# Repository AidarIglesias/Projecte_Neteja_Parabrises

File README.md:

# Projecte Eines De Disseny  
## Sistema de Neteja-Parabrises D'Un Automobil  
###### David Miravent, Biel Hornas, Aidar Iglesias  

### Objectiu  
Aquest projecte te com a objectiu dissenyar el l'entorn electronic que conforma el sistema de neteja-parabrises d'un automobil.  

El projecte estara dividit en 7 parts:  

1. Diagrama de blocs i components
2. Esquematic i simulacions
3. Placement i routing (layout v1)
4. Pre-entega (layout v2)
5. Entrega final (layout v3)
6. Muntatge i soldadura
7. Test PCB  

----  

### Caracteristiques i epecificacions  
El sistema de neteja-parabrises te com a caracteristica principal, com ja diu el seu nom, netejar la lluna del parabrises. Com que aquest sistema sera part d'un conjunt de ECUs (Electronic Control Unit) d'un automobil, hi ha un serie d'elements que tots ells tindran en comu:  

* Una etapa de regulacio de tensio (es fara servir [L78S05CV])
* Un microcontrolador (es fara servir un [PIC18F2580] de 28 pins) encarregat del control del nostre modul i de la comunicacio amb els altres
* Un bus de programacio i debug del microcontrolador
* Un bus [CAN] que permet la comunicacio sincrona amb els altres moduls
* Un bus [I2C] (o be [SPI]) per a la comunicacio sincrona interna del nostre modul
* Un bus de comunicacio [USART] que permet monitoritzar el sistema des d'un ordinador extern
* Una botonera per permetre la interaccio entre l'usuari i el modul

El sistema ha de complir les seguents **especificacions**:  

* Dos motors amb el seu final de carrera
* Dues bombes de liquid neteja-parabrises
* Sensor digital de pluja
* Calefactor del vidre

----  

### Funcionament  

El sistema al complet estara controlat per el microcontrolador. Per al moviment dels neteja parabrises, es faran servir dos motors, un per davant i un per darrere. Aquests motors estaran controlats per uns drivers, els quals subministren el corrent necessari per activar uns reles que faran girar els motors en un sentit o en l'altre. Quan l'usuari desitgi o quan el sensor de pluja detecti pluja, el microcontrolador enviara el senyal d'activacio dels motors. Tambe s'incloura un sistema de final de carrera, que indicara quan s'ha acabat el trajecte de la escombreta del neteja-parabrises i la fara canviar de sentit.  

El sistema tambe implementa dues bombes de liquid neteja-parabrises, cadascuna d'elles controlada per un driver i un rele. Aquestes s'activaran quan el conductor ho desitgi i funcionaran de la mateixa manera que el neteja-parabrises: mitjançant un motor.  

Hi haura un mode de neteja automatic, accionat per un sensor digital de pluja. Quan es detecti pluja. Aleshores, el neteja-parabrises es posara en funcionament.  

Hi ha quatre opcions a escollir:
* Activar motor neteja-parabrises davanter
* Activar motor neteja-parabrises darrere
* Automatic (El sensor de pluja activa els neteja-parabrises)  

Mes enlla d'aquests 3 modes de funcionament, si aixi ho desitja, l'usuari pot activar les bombes de liquid manualment. Addicionalment, pot fer que les escombretes fagin una sola passada, tambe amb activacio manual.  

----  

### Diagrama de Blocs  

.png)  
**Figura 3.** Versio 4 del diagrama de blocs - 13.04.2023.  

----  

### Taula de funcionament dels reles  

| **EnableM1** | **DriverM1** | **MOTOR 1** |  
| ------------ | ------------ | ----------- |  
| 0            | 0            | 0           |  
| 0            | 1            | 0           |  
| 1            | 0            | 0           |  
| 1            | 1            | 1           |  

**Taula 1.** Taula del funcionament dels reles del motor neteja-parabrises davanter.  

| **EnableM2** | **DriverM2** | **MOTOR 2** |  
| ------------ | ------------ | ----------- |  
| 0            | 0            | 0           |  
| 0            | 1            | 0           |  
| 1            | 0            | 0           |  
| 1            | 1            | 1           |  

**Taula 2.** Taula del funcionament dels reles del motor neteja-parabrises del darrere.

---  

### Components  

| Ref. | Descripcio | Datasheet |  
| ---- | ---------- | --------- |  
| PIC18F2580 | 28-Pin High Performance, Enhanced FLASH Microcontroller with CAN. S'encarrega del control integral del sistema. | [PIC18F2580] |  
| TCAN1042 | TCAN1042 Fault Protected CAN Transceiver with CAN FD. L'utilitzarem per a la comunicacio entre moduls independents. | [TCAN1042] |  
| LM1117-5.0 | 2A positive voltage regulator IC. Regulador LDO lineal de tres terminals, corrent nominal 2A i sortida a 5V. | [L78S05CV] |  
| ABLS2-8.000MHZ-D4Y-T | Low Profile Surface Mount Microprocessor Crystal. L'usarem com a font de senyal sincron de referencia per al microcontrolador. Es de 8MHz. | [ABLS2-8MHZ]  
| V23076A1001C133 | Automotive, PCB Single Power Relay K (Sealed) with wide voltage range and limiting continuous current 45A. Utilitzarem aquest rele per a les aplicacions de potencia, com ara la commutacio dels motors, de les bombes i del calefactor. | [V23076A1001C133]  
| BC817-25 | NPN general purpose transistor used for switching and amplification. Features high current (max. 500 mA) and low voltage (max. 45 V). Transistor bipolar NPN que farem servir per a amplificar el corrent de commutacio dels reles. | [BC817-25] |  
| YL-83 | Rain and snow are quickly and accurately detected with the YL-83 Rain Detector. L'implementarem de manera que quan detecti pluja, els neteja-parabrises s'accionin automaticament. | [YL-83] |  
| LM393 | Comparator with lower offset voltage, higher supply voltage capability, lower supply current, lower input bias current, lower propagation delay, and improved 2 kV ESD performance and input ruggedness through dedicated ESD clamps. Comparador que farem servir a l'hora de detectar si plou o no. | [LM393] |  
| 3362-¼” Square Trimpot | Trimming Potentiometer. Withstands harsh environments and immersion cleaning processes. Potenciometre que usarem per adjustar el llindar del sensor de pluja. | [3362-¼” Square Trimpot]  
| Flexible Heaters 78000 Series | Truly transparent, no wires in clear view area, optical grade, thin-film polyester, low power consumption for use with battery or line power. Tires conductores que tenen com a objectiu escalfar la lluna del darrere de l'automobil. | [Flexible Heaters 78000 Series] |  
| WLD4383 | Motor reductor _sinfin_ 12VDC, corrent nominal de 2A, velocitat nominal de 44rmp i una potencia de 12.5W. | [WLD4383]  
| EHDB9MF | Connector DB-9 de entrada-sortida de la comunicacio CAN. | [EHDB9MF] |  

----
### Historial de canvis  

| Data | Autor | Descripcio |  
| ---- | ----- | ---------- |  
| 23.03.2023 | David Miravent | Tramesa de la tasca per a la primera versio de la presentacio. |  
| 27.03.2023 | Biel Hornas, David Miravent, Aidar Iglesias | Diagrama de blocs: Eliminat el sensor de temperatura. Eliminats els busos i transceivers CAN que estaven connectats entre els sensors + els que connectaven el PIC amb els motors. Modificada la botonera. Afegit el nou bus CAN. Modificat el connector de programacio i debug. Modificats els drivers i els components de potencia. Modificat l'oscil·lador. Afegit el driver del sensor de pluja. Afegits els consums individuals de cada component. Inclosos els pins de les connexions PIC-periferics. |  
| 28.03.2023 | Biel Hornas, David Miravent, Aidar Iglesias | Presentacio: Actualitzada la llista de components (diap. 5, 6). Inclosos els parametres d'interes per a cada component (diap. 8 - 18). Actualitzat el diagrama de blocs (diap. 19). |  
| 30.03.2023 | Biel Hornas, David Miravent | Realitzacio simulacions regulador de tensio + sensor de pluja, modificat el esquematic (sch) del projecte : s'han afegit totes les etapes del sistema en estructura de fulles jerarquiques. |  
| 31.03.2023 | Aidar Iglesias | README: actualitzada la imatge del diagrama de blocs. Corregit el valor de consum del PIC. Modificat el connector de la botonera |  
| 04.04.2023 | Biel Hornas | Actualitzada la jerarquia de fulls de l'esquematic: *Alimentacio*, *Digital*, *Analog* i *Potencia*. Sensor de pluja ficat tot en una mateixa capsa. Modificada la botonera: s'han eliminat els interruptors, ja que son externs a la placa. Corregits els noms de les *nets* a l'esquematic dels drivers de motors, que causaven curt-circuits. Canviat el model dels reles a V23086C1001A403, ja que te millor simbol i footprint. Modificat el connector d'alimentacio a l'esquematic del regulador. |  
| 05.04.2023 | David Miravent, Aidar Iglesias | Esquematic: Afegit titol al sheet *root*: **Sistema de Neteja-parabrises**. Modificada la ubicacio del LED d'alimentacio: del PIC al regulador. Reset Manual i Oscil·lador connectats directament al PIC. Corregides les connexions del connector DB-9 del bus CAN. Afegit connector DB-9 per al modul de comunicacio USART. Moduls de comunicacio CAN i USART connectats directament al PIC. |  
| 07.05.2023 | Aidar Iglesias | Esquematic: Canviat el regulador de tensio: LM1117-5 a L78S05CV (corrent de sortida major). Canviats els valors de les capacitats d'entrada i sortida del regulador. Corregides les connexions dels drivers de l'apartat de potencia (feien curt-circuit de la bateria a terra). Diagrama de blocs: actualitzat el regulador de tensio de LM1117 a L78S05CV. Corregits els valors de consum (PIC, LM393, TCAN1042) Presentacio: Actualitzat el diagrama de blocs. |  
| 10.04.2023 | David Miravent, Biel Hornas, Aidar Iglesias | Esquematic: Afegides les ferrites per separar el GND de potencia i el GND general. Layout: dissenyada la primera versio del Layout. |  
| 17.04.2023 | David Miravent, Biel Hornas, Aidar Iglesias | Esquematic: Canviat el node de VBAT al node despres del diode 1n4002 (protegit de canvis de polaritats). Corregida la separacio de GNDPWR i GND al regulador. Canviat el tipus de connector dels motors de pin-header a screwdriver. Canviat el divisor de tensio del sensor de pluja. |  
| 24.04.2023 | Biel Hornas, Aidar Iglesias, David Miravent | Esquematic: afegit el sistema de final de carrera. Assignades les xarxes dels BJTs a la classe ANG. Layout: Canviats totes les capacitats i totes les resistencies a SMD. Dissenyats els copper pours de manera que quedin regulars i uniformes per tota la PCB. Disminuit el tamany de les pistes de potencia. Recolocats alguns components. Re-routing general de la part de potencia. Afegides les llagrimes a les connexions pista-via i pista-pad.  
| 26.04.2023 | David Miravent, Biel Hornas, Aidar Iglesias | Generacio dels fitxers BOM i calcul del pressupost de la placa en tirada curta i llarga. Presentacio: Actualitzades les diapositives de l'esquematic i del layout. |  

[L78S05CV]:(https://www.google.com/url?sa=t&rct=j&q=&esrc=s&source=web&cd=&cad=rja&uact=8&ved=2ahUKEwizl6HozLD-AhWBLOwKHajVC9oQFnoECBYQAQ&url=https%3A%2F%2Fwww.mouser.com%2FProductDetail%2FSTMicroelectronics%2FL78S05CV%3Fqs%3DsepekKm5O7lXLQm2U%252FAl6g%253D%253D&usg=AOvVaw0-vxvqoBEyTqxAWQKdSOBr)
[PIC18F2580]:(https://www.google.com/url?sa=t&rct=j&q=&esrc=s&source=web&cd=&cad=rja&uact=8&ved=2ahUKEwjDqqnf-fv9AhWAXaQEHbvXCRAQFnoECBAQAQ&url=http%3A%2F%2Fww1.microchip.com%2Fdownloads%2Fen%2Fdevicedoc%2F39637d.pdf&usg=AOvVaw2IUnS-oBxKa8P9iGtzo3Zw)
[CAN]:(https://www.google.com/url?sa=t&rct=j&q=&esrc=s&source=web&cd=&cad=rja&uact=8&ved=2ahUKEwiok8Se-vv9AhVSUKQEHZ1pCZgQFnoECAwQAQ&url=https%3A%2F%2Fwww.ti.com%2Flit%2Fpdf%2Fsloa101&usg=AOvVaw2UOzkNpIhXCxiMwoktDuf0)  
[I2C]:(https://www.google.com/url?sa=t&rct=j&q=&esrc=s&source=web&cd=&cad=rja&uact=8&ved=2ahUKEwjWtri9-vv9AhV0UKQEHW7hC54QFnoECA4QAw&url=https%3A%2F%2Flearn.sparkfun.com%2Ftutorials%2Fi2c%2Fall&usg=AOvVaw2qpJdC-UXOjJ03YiNE41H4)
[SPI]:(https://www.google.com/url?sa=t&rct=j&q=&esrc=s&source=web&cd=&cad=rja&uact=8&ved=2ahUKEwjrloTV-vv9AhUyU6QEHYIMDGgQFnoECAwQAQ&url=https%3A%2F%2Flearn.sparkfun.com%2Ftutorials%2Fserial-peripheral-interface-spi%2Fall&usg=AOvVaw13lzzbG5R14CmXp8TmZ-Gi)
[USART]:(https://www.google.com/url?sa=t&rct=j&q=&esrc=s&source=web&cd=&cad=rja&uact=8&ved=2ahUKEwiqn8Pz-vv9AhWSSKQEHeZICZEQFnoECCwQAQ&url=https%3A%2F%2Fwww.ti.com%2Fsc%2Fdocs%2Fproducts%2Fmicro%2Fmsp430%2Fuserguid%2Fag_12.pdf&usg=AOvVaw08SU_ut2QHKfywglni0Si5)
[TCAN1042]:(https://www.ti.com/lit/ds/symlink/tcan1042hv.pdf?ts=1679998738764&ref_url=https%253A%252F%252Fwww.ti.com%252Fproduct%252FTCAN1042HV%253Futm_source%253Dgoogle%2526utm_medium%253Dcpc%2526utm_campaign%253Dti-null-null-xref-cpc-pf-google-wwe%2526utm_content%253Dxref%2526ds_k%253D%257B_dssearchterm%257D%2526DCM%253Dyes%2526gclid%253DCjwKCAjwoIqhBhAGEiwArXT7K-KRBrhZ83RLTsUGoJig2M_4bRYp_h0gqncf8DgUPU1i8GLFYlaWCBoCYGYQAvD_BwE%2526gclsrc%253Daw.ds)  
[ABLS2-8MHZ]:(https://www.mouser.es/datasheet/2/3/ABLS2-1775116.pdf)  
[V23076A1001C133]:(https://www.farnell.com/datasheets/2243264.pdf)  
[BC817-25]:(https://pdf1.alldatasheet.com/datasheet-pdf/view/16111/PHILIPS/BC817-25.html)  
[YL-83]:(https://urolakostapk.files.wordpress.com/2016/10yl-83-rain-detector-datasheet_low.pdf)  

[LM393]:(https://www.ti.com/lit/ds/symlink/lm393.pdf?ts=1680064194729&ref_url=https%253A%252F%252Fwww.ti.com%252Fproduct%252FLM393)  
[3362-¼” Square Trimpot]:(https://www.farnell.com/datasheets/3171216.pdf)  
[Flexible Heaters 78000 Series]:(https://www.mouser.es/datasheet/2/187/honeywell-sensing-flexible-heaters-line-guide-0090-1525721.pdf)  
[WLD4383]:(https://transmotec.es/product/WLD4383-12-61/)  
[EHDB9MF]:(https://www.switchcraft.com/assets/1/24/EHDB9_EHHD15_SERIES_CD.PDF?4882)

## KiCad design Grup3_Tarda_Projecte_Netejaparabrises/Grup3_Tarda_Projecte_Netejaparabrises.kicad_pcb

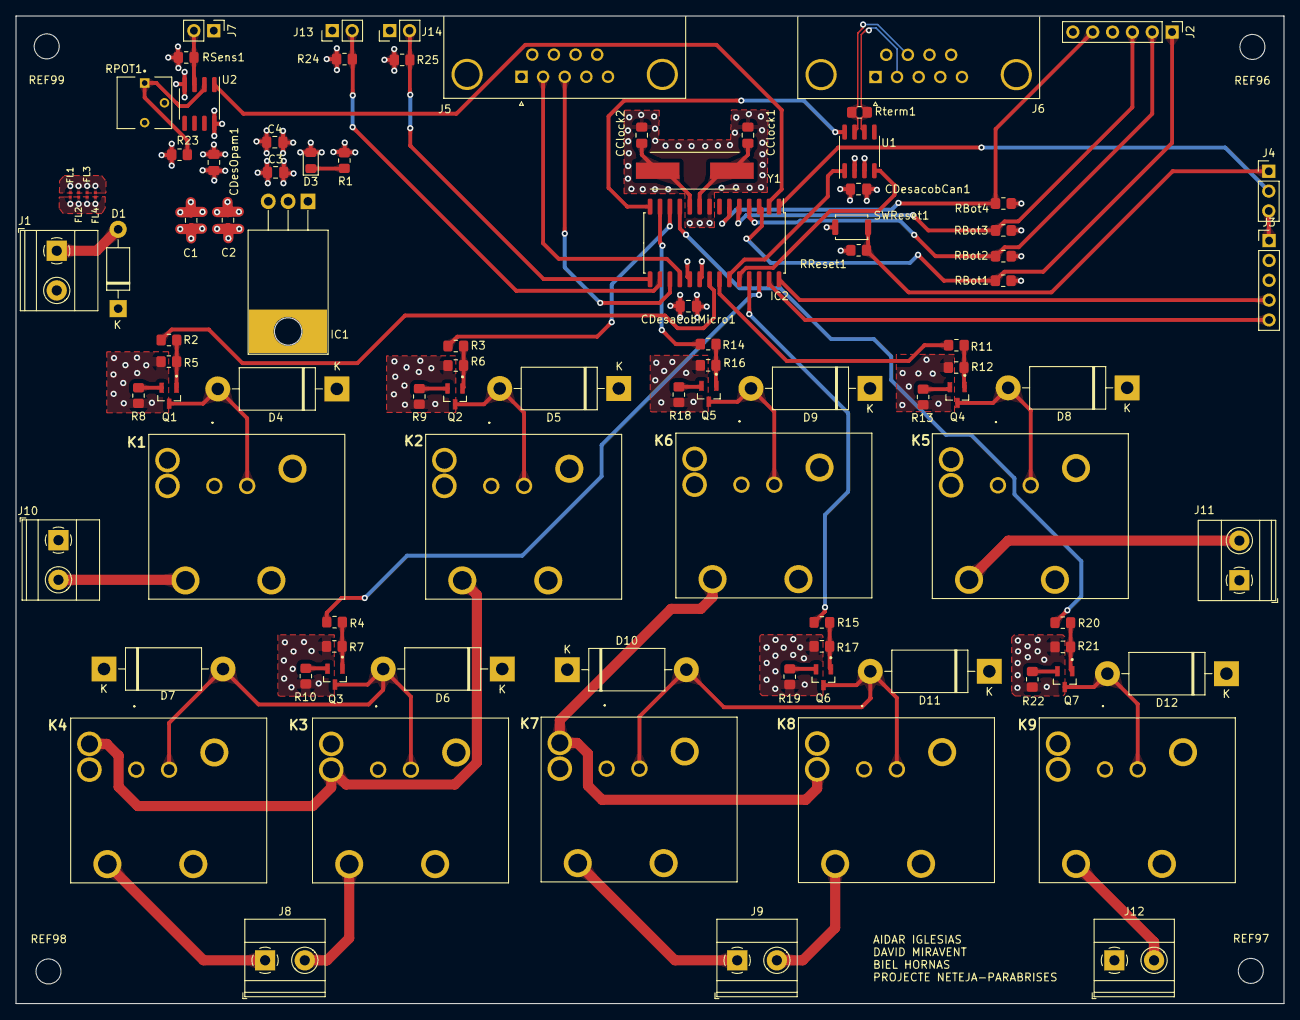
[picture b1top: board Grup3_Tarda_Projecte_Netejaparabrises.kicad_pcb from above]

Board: 4 copper layers, 162.4 x 126.5 mm, 97 parts (0 on the bottom side), 66 nets.

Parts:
C1, C4: 100n; C_0805_2012Metric_Pad1.18x1.45mm_HandSolder
C2: 0.33u; C_0805_2012Metric_Pad1.18x1.45mm_HandSolder
C3: 0.1u; C_0805_2012Metric_Pad1.18x1.45mm_HandSolder
CClock1, CClock2: 22p; C_0805_2012Metric_Pad1.18x1.45mm_HandSolder
CDesOpam1: 100n; C_0805_2012Metric_Pad1.18x1.45mm_HandSolder
CDesacobCan1: 100n; C_0805_2012Metric_Pad1.18x1.45mm_HandSolder
CDesacobMicro1: 100n; C_0805_2012Metric_Pad1.18x1.45mm_HandSolder
D1: 1N4002; D_DO-41_SOD81_P10.16mm_Horizontal
D3: LED; LED_0805_2012Metric_Pad1.15x1.40mm_HandSolder
D4, D5, D6, D7, D8, D9, D10, D11, D12: 1N5400; D_DO-201AD_P15.24mm_Horizontal
FL1, FL2, FL3, FL4: BLM03HD331SZ1D; BEADC0603X33N
IC1: L78S05CV; TO-220-3_Horizontal_TabDown_mod
IC2: PIC18F258-I_SO; SOIC-28W_7.5x17.9mm_P1.27mm
J1, J8, J9, J10, J11, J12: Screw_Terminal_01x02; TerminalBlock_Phoenix_MKDS-1,5-2-5.08_1x02_P5.08mm_Horizont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
J2: BOTONERA; PinHeader_1x06_P2.54mm_Vertical
J3: PROGRAMMING CON; PinHeader_1x05_P2.54mm_Vertical
J4: JP1; PinHeader_1x03_P2.54mm_Vertical
J5, J6: DE9_Plug_MountingHoles; DSUB-9_Female_Horizontal_P2.77x2.84mm_EdgePinOffset4.94mm_H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
J7: CONEXIOSENSOR; PinHeader_1x02_P2.54mm_Vertical
J13, J14: FINAL DE CARRERA; PinHeader_1x02_P2.54mm_Vertical
K1, K2, K3, K4, K5, K6, K7, K8, K9: 1393280-6; V23076A1001C133
Q1, Q2, Q3, Q4, Q5, Q6, Q7: BC817-25_RF; SOT95P237X112-3N
R1: 220R; R_0805_2012Metric_Pad1.20x1.40mm_HandSolder
R2, R3, R4, R11, R14, R15, R20: 620.3R; R_0805_2012Metric_Pad1.20x1.40mm_HandSolder
R5, R6, R7, R12, R16, R17, R21: 319.6R; R_0805_2012Metric_Pad1.20x1.40mm_HandSolder
R8, R9, R10, R13, R18, R19, R22: 13.4R; R_0805_2012Metric_Pad1.20x1.40mm_HandSolder
R23: 10k; R_0805_2012Metric_Pad1.20x1.40mm_HandSolder
R24, R25: 22k; R_0805_2012Metric_Pad1.20x1.40mm_HandSolder
RBot1, RBot2, RBot3, RBot4: 22k; R_0805_2012Metric_Pad1.20x1.40mm_HandSolder
REF96, REF97, REF98, REF99: MountingHole_3.2mm_M3_ISO7380
RPOT1: 10k; TRIM_3362P-1-103
RReset1: 4.7k; R_0805_2012Metric_Pad1.20x1.40mm_HandSolder
RSens1: 1k; R_0805_2012Metric_Pad1.20x1.40mm_HandSolder
Rterm1: 120R; R_0805_2012Metric_Pad1.20x1.40mm_HandSolder
SWReset1: SW_Push; SW_Push_SPST_NO_Alps_SKRK
U1: Value; SOIC-8_3.9x4.9mm_P1.27mm
U2: LM393; SOIC-8_3.9x4.9mm_P1.27mm
Y1: ABLS2-8.000MHZ-D4Y-T; XTAL_ABLS2-8.000MHZ-D4Y-T

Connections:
+VCC: C3.1, C4.1, CDesOpam1.1, CDesacobCan1.1, CDesacobMicro1.1, D3.2 (A), IC1.3, IC2.20 (VDD), J3.2, J7.1, R23.1, R24.1, R25.1, RBot1.1, RBot2.1, RBot3.1, RBot4.1, RReset1.1, U1.3 (VCC), U2.8 (V+)
/Alimentacio/Vbat: D1.2 (A), J1.1
/Alimentacio/Vled: D3.1 (K), R1.1
/Analog/Vsensibilitat: R23.2, RPOT1.1, U2.2 (-)
/Analog/Vsensor: J7.2, RSens1.1, U2.3 (+)
/Digital/CAN+: J6.2, Rterm1.1, U1.6 (CANL)
/Digital/CAN-: J6.7, Rterm1.2, U1.7 (CANH)
/Digital/CANRX: IC2.24 (RB3/CANRX), U1.4 (RXD)
/Digital/CANTX: IC2.23 (RB2/CANTX/INT2), U1.1 (TXD)
/Digital/MCLR: IC2.1 (~MCLR/VPP), J4.2
/Digital/PROG_MCLR: J3.1, J4.3
/Digital/Rx: IC2.18 (RC7/RX/DT), J5.2
/Digital/Tx: IC2.17 (RC6/TX/CK), J5.3
/Digital/Vboto1: IC2.3 (RA1/AN1), J2.1, RBot1.2
/Digital/Vboto2: IC2.4 (RA2/AN2/VREF-), J2.2, RBot2.2
/Digital/Vboto3: IC2.5 (RA3/AN3/VREF+), J2.3, RBot3.2
/Digital/Vboto4: IC2.6 (RA4/T0CKI), J2.5, RBot4.2
/Digital/Vfin_back: IC2.15 (RC4/SDI/SDA), J14.2, R25.2
/Digital/Vfin_front: IC2.16 (RC5/SDO), J13.2, R24.2
/Digital/Vsw: J4.1, RReset1.2, SWReset1.1
/Digital/XTAL1: CClock1.1, IC2.9 (OSC1/CLKI), Y1.1
/Digital/XTAL2: CClock2.1, IC2.10 (OSC2/CLKO/RA6), Y1.2
/Potencia/Vb_EN1: Q2.1, R3.2, R6.2
/Potencia/Vb_EN2: Q5.1, R14.2, R16.2
/Potencia/Vb_b1: Q1.1, R2.2, R5.2
/Potencia/Vb_b2: Q4.1, R11.2, R12.2
/Potencia/Vb_lu: Q7.1, R20.2, R21.2
/Potencia/Vb_m1: Q3.1, R4.2, R7.2
/Potencia/Vb_m2: Q6.1, R15.2, R17.2
/Potencia/Vc_EN1: D5.2 (A), K2.2, Q2.3
/Potencia/Vc_EN2: D9.2 (A), K6.2, Q5.3
/Potencia/Vc_b1: D4.2 (A), K1.2, Q1.3
/Potencia/Vc_b2: D8.2 (A), K5.2, Q4.3
/Potencia/Vc_lu: D12.2 (A), K9.2, Q7.3
/Potencia/Vc_m1: D6.2 (A), D7.2 (A), K3.2, K4.2, Q3.3
/Potencia/Vc_m2: D10.2 (A), D11.2 (A), K7.2, K8.2, Q6.3
/Potencia/Ve_EN1: Q2.2, R9.2
/Potencia/Ve_EN2: Q5.2, R18.2
/Potencia/Ve_b1: Q1.2, R8.2
/Potencia/Ve_b2: Q4.2, R13.2
/Potencia/Ve_lu: Q7.2, R22.2
/Potencia/Ve_m1: Q3.2, R10.2
/Potencia/Ve_m2: Q6.2, R19.2
DriverB1: IC2.21 (RB0/INT0), R2.1
DriverB2: IC2.22 (RB1/INT1), R11.1
DriverLuneta: IC2.11 (RC0/T1OSO/T1CKI), R20.1
DriverM1: IC2.26 (RB5/PGM), R4.1
DriverM2: IC2.25 (RB4), R15.1
EN1: K2.4, K3.5, K4.3
EN2: K6.4, K7.3, K8.5
EnableM1: IC2.12 (RC1/T1OSI), R3.1
EnableM2: IC2.13 (RC2/CCP1), R14.1
GND: C3.2, C4.2, CClock1.2, CClock2.2, CDesOpam1.2, CDesacobCan1.2, CDesacobMicro1.2, FL1.2, FL2.2, FL3.2, FL4.2, IC2.8 (VSS_1), IC2.19 (VSS_2), J2.4, J2.6, J3.3, J5.5, J6.6, J13.1, J14.1, R1.2, RPOT1.2, RPOT1.3, RSens1.2, SWReset1.2, U1.2 (GND), U2.4 (V-)
GNDPWR: C1.2, C2.2, FL1.1, FL2.1, FL3.1, FL4.1, IC1.2, J1.2, J10.1, J11.1, J12.1, K1.3, K2.3, K3.3, K4.5, K5.3, K6.3, K7.5, K8.3, K9.3, R5.1, R6.1, R7.1, R8.1, R9.1, R10.1, R12.1, R13.1, R16.1, R17.1, R18.1, R19.1, R21.1, R22.1
PGC: IC2.27 (RB6/PGC), J3.5
PGD: IC2.28 (RB7/PGD), J3.4
STB: IC2.14 (RC3/SCK/SCL), U1.8 (STB)
Sensordig_o: IC2.2 (RA0/AN0/CVREF), U2.1
VBAT: C1.1, C2.1, D1.1 (K), D4.1 (K), D5.1 (K), D6.1 (K), D7.1 (K), D8.1 (K), D9.1 (K), D10.1 (K), D11.1 (K), D12.1 (K), IC1.1, K1.1, K1.5, K2.1, K2.5, K3.1, K4.1, K5.1, K5.5, K6.1, K6.5, K7.1, K8.1, K9.1, K9.5
VBOMBA1: J10.2, K1.4
VBOMBA2: J11.2, K5.4
VLUNETA: J12.2, K9.4
VMOT1+: J8.2, K3.4
VMOT1-: J8.1, K4.4
VMOT2+: J9.2, K8.4
VMOT2-: J9.1, K7.4

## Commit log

2023-03-28 creacio_projecte
2023-03-28 actualitzacio_readme
2023-03-28 canvi de nom del README
2023-03-29 models
2023-03-29 canvis README 30-03-2023
2023-03-30 canvis prova
2023-03-30 canvis llibreries i requeriments
2023-03-30 canvis llibreries i projecte
2023-03-30 simulacioRegulador
2023-03-30 canvis esquematic
2023-03-30 DriverSensorPluja
2023-03-31 Backlink to CADLAB.io has been added.
2023-03-31 31-03-2023
2023-03-31 canvis README 31-03-2023
2023-04-03 Modificat nets dels drivers de motors bombes... botonera i sensor de pluja millorats i amb connectors
2023-04-05 Canvis estructura general, reles, comunicacacions i clock
2023-04-05 canvis schematic 05-04-23
2023-04-07 canvis schematic i README 07-04-2023
2023-04-07 canvis reles 07-04-2023
2023-04-08 GNDS 08042023
2023-04-08 definitiuEsquematicsenseFootprints
2023-04-08 definitiuEsquematicsenseFootprints2
2023-04-10 Layout Esquema
2023-04-11 esborrats sheets vells
2023-04-11 Modificacions finals assignacio footprints
2023-04-11 Sense errors de visualització, preparat pel layout
2023-04-11 canvis menors a esquematic i README
2023-04-11 mes canvis README
2023-04-12 canvis menors esquematic
2023-04-12 canvis reles
2023-04-13 Layout 3
2023-04-17 canvis divisor sensor de pluja, node vbat protegit, connector de motors, README
2023-04-18 placement
2023-04-18 powersilkscreen
2023-04-18 plans de massa i alimentacio layout
2023-04-19 routing v1 sense acabar
2023-04-19 Routing
2023-04-20 canvis menors layout
2023-04-20 layout modificat a 2 capes
2023-04-25 placing rooting
2023-04-25 redefinicio copper pours, rerouting, final de carrera i teardrops
2023-04-26 afegits els finals de carrera dels motors
2023-04-26 canvi de posicio de ferrites i connectors reset debug
2023-04-26 Fitxer BOM
2023-04-26 canvis diagrama de blocs i README
2023-04-26 fitxer BOM amb footprints i mes
2023-04-26 canvi de fitxer BOM
2023-04-27 definitiu
2023-04-27 modificacions BOM
2023-04-27 gerbers i 3d
2023-04-27 commit final
